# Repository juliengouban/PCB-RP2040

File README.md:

# PCB-RP2040

We've realized an electronic board based on the RP2040.
This microcontroller has 2 MB of flash memory, providing ample storage space for programs and data. It has 26 digital I/O pins, 3 of which can be used as analog inputs.
The RP20240 is used for the Raspberry Pico board and is programmable in micro-Python or directly with Arduino Ide.
We developed the board on Kicad and had it manufactured on jpclb. It costs around 17 euros per board, and is a 2-layer board measuring 2.7cm x 2 cm. You can find the files on our github.

<h1> Electronic diagram</h1>
We'll now take a closer look at how our electronic board works: 

For powering the circuit, we've used a Micro USB type B connector to supply our board with 5V. As the RP2040 uses 3.3V, we've fitted a regulator to convert 5V to +3.3V: 

This is where you'll find the 128-megabit flash memory to store the program. The 2-pin connector allows you to force USB boot:

The 12Mhz crystal provides the clock for our RP2040 microcontroller:

We have added a LED to be programmed on GPIO18 to check that our card is working properly: 

Finally, we have the RP2040 microncontroller. It is supplied with 3.3V with decoupling capacitors:

<h1>PCB Design</h1>

The board is a 2-layer design. On the top you can see the 3.3V regulator and the Micro-USB type B connector.
In the middle of the board you'll find the flash memory and the RP2040 microcontroller.
At the bottom of the board you'll find the 2-pin USB boot connector and the 12Mhz quartz crystal.
A ground plane has been created on the TOP layer to connect all the GNDs together.

Here are the 3d and top layer views of the PCB:

Here is a 3d view of the PCB:

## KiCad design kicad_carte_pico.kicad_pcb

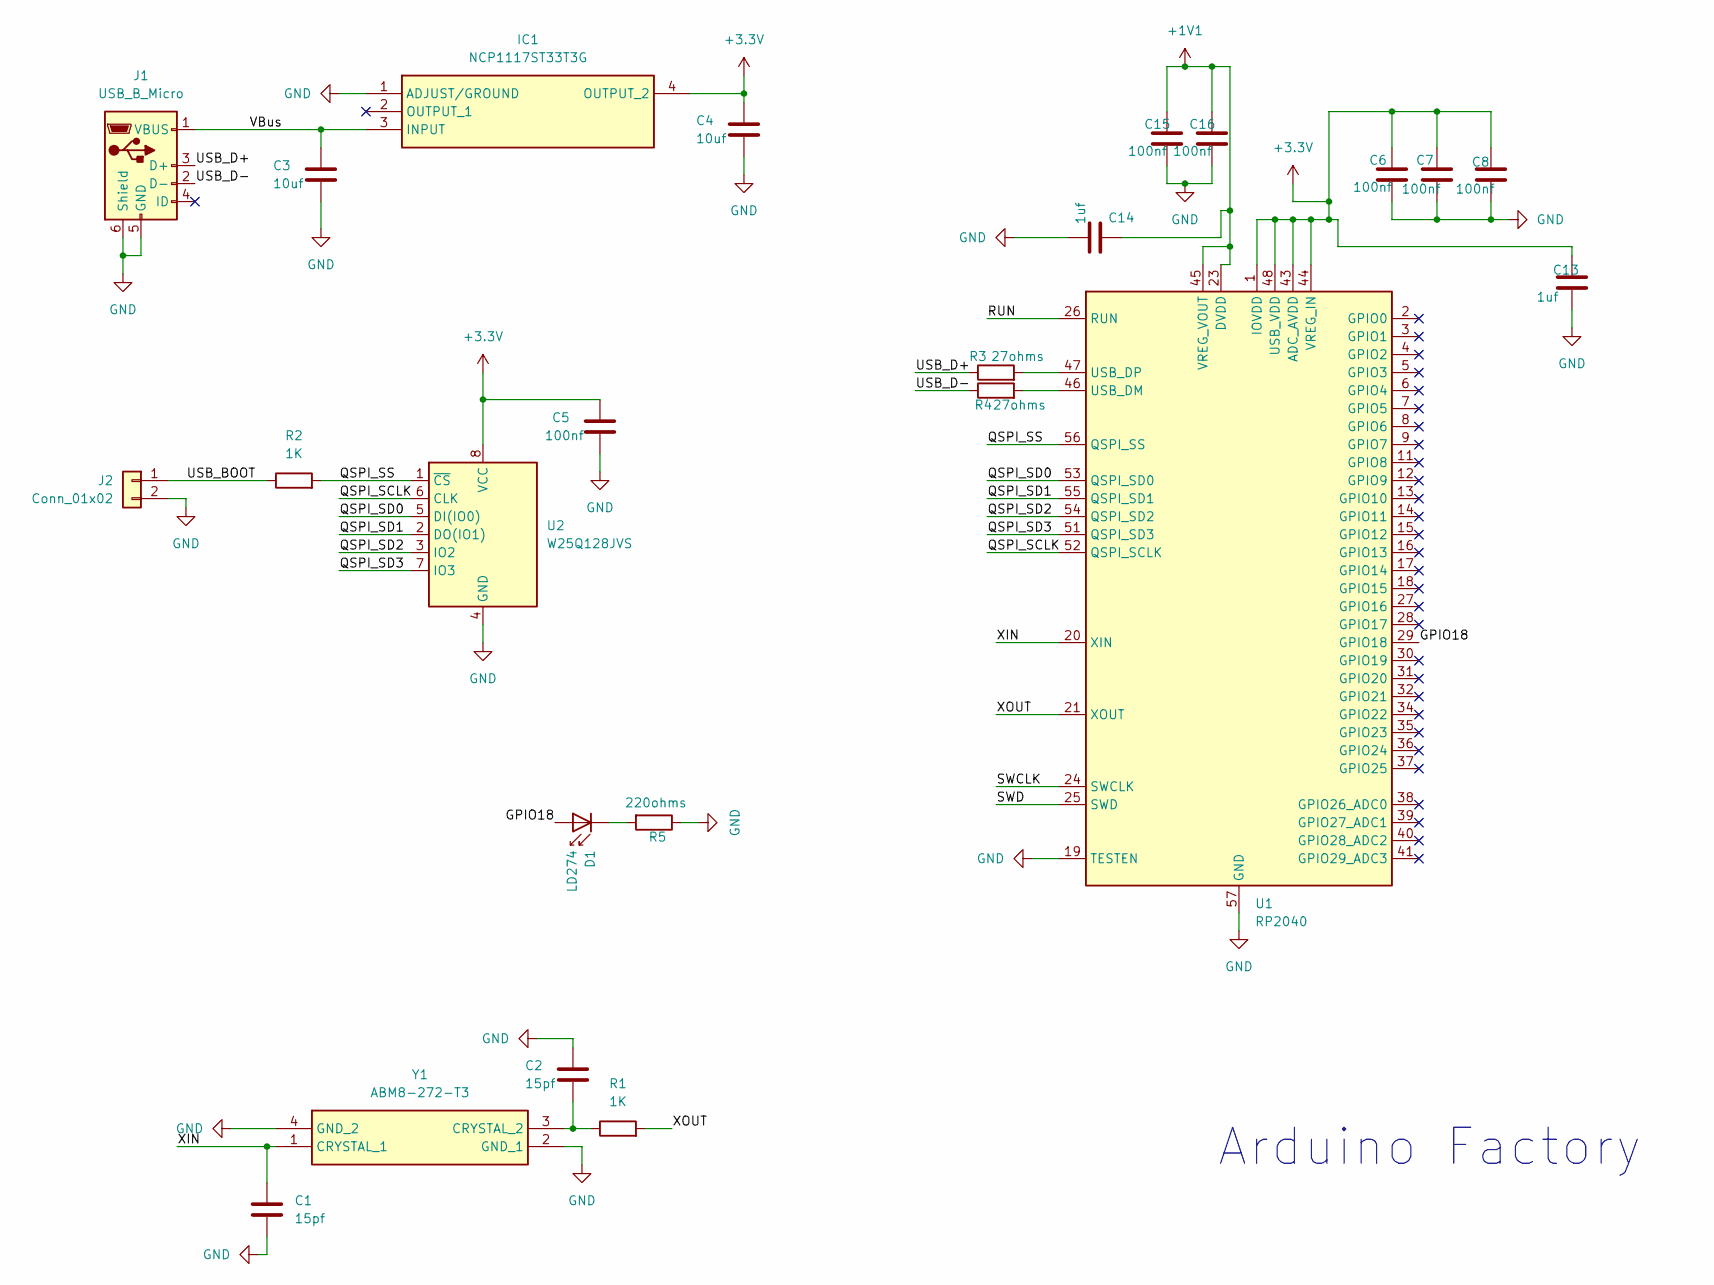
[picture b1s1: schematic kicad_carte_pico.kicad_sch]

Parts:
C1, C2: 15pf; C_0402_1005Metric
C3, C4: 10uf; C_0402_1005Metric
C5, C6, C7, C8, C15, C16: 100nf; C_0402_1005Metric
C13, C14: 1uf; C_0402_1005Metric
D1: LD274; LED_0402_1005Metric
IC1: NCP1117ST33T3G; SOT230P700X180-4N; Manufacturer_Part_Number NCP1117ST33T3G; Mouser Part Number 863-NCP1117ST33T3G
J1: USB_B_Micro; USB_Micro-B_Amphenol_10103594-0001LF_Horizontal
J2: Conn_01x02; PinHeader_1x02_P1.27mm_Vertical
R1, R2: 1K; R_0402_1005Metric
R3, R4: 27ohms; R_0402_1005Metric
R5: 220ohms; R_0402_1005Metric
U1: RP2040; QFN-56-1EP_7x7mm_P0.4mm_EP3.2x3.2mm
U2: W25Q128JVS; SOIC-8_5.23x5.23mm_P1.27mm
Y1: ABM8-272-T3; ABM8272T3; Mouser Part Number 815-ABM8-272-T3

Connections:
+1V1: C14.1, C15.1, C16.1, U1.23 (DVDD), U1.45 (VREG_VOUT), U1.50 (DVDD)
+3.3V: C4.1, C5.1, C6.1, C7.1, C8.1, C13.1, IC1.4 (OUTPUT_2), U1.1 (IOVDD), U1.10 (IOVDD), U1.22 (IOVDD), U1.33 (IOVDD), U1.42 (IOVDD), U1.43 (ADC_AVDD), U1.44 (VREG_IN), U1.48 (USB_VDD), U1.49 (IOVDD), U2.8 (VCC)
/GPIO18: D1.2 (A), U1.29 (GPIO18)
/QSPI_SCLK: U1.52 (QSPI_SCLK), U2.6 (CLK)
/QSPI_SD0: U1.53 (QSPI_SD0), U2.5 (DI(IO0))
/QSPI_SD1: U1.55 (QSPI_SD1), U2.2 (DO(IO1))
/QSPI_SD2: U1.54 (QSPI_SD2), U2.3 (IO2)
/QSPI_SD3: U1.51 (QSPI_SD3), U2.7 (IO3)
/QSPI_SS: R2.2, U1.56 (QSPI_SS), U2.1 (~CS)
/RUN: U1.26 (RUN)
/SWCLK: U1.24 (SWCLK)
/SWD: U1.25 (SWD)
/USB_BOOT: J2.1, R2.1
/USB_D+: J1.3 (D+), R3.1
/USB_D-: J1.2 (D-), R4.1
/VBus: C3.1, IC1.3 (INPUT), J1.1 (VBUS)
/XIN: C1.1, U1.20 (XIN), Y1.1 (CRYSTAL_1)
/XOUT: R1.2, U1.21 (XOUT)
GND: C1.2, C2.1, C3.2, C4.2, C5.2, C6.2, C7.2, C8.2, C13.2, C14.2, C15.2, C16.2, IC1.1 (ADJUST/GROUND), J1.5 (GND), J1.6 (Shield), J2.2, R5.1, U1.19 (TESTEN), U1.57 (GND), U2.4 (GND), Y1.2 (GND_1), Y1.4 (GND_2)
unnamed: D1.1 (K), R5.2
unnamed: R4.2, U1.46 (USB_DM)
unnamed: R3.2, U1.47 (USB_DP)
unnamed: C2.2, R1.1, Y1.3 (CRYSTAL_2)

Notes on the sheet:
Arduino Factory

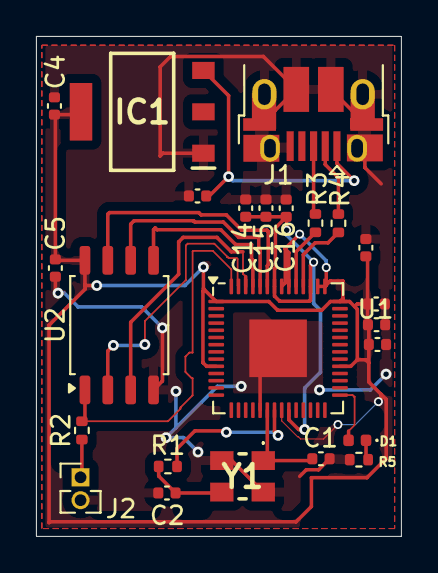
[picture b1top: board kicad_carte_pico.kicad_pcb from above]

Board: 2 copper layers, 20.3 x 27.8 mm, 24 parts (0 on the bottom side), 20 nets.

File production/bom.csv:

Designator,Footprint,Quantity,Value,LCSC Part #
"C1, C2",0402,2,15pf,
"C13, C14",0402,2,1uf,
"C15, C16, C5, C6, C7, C8",0402,6,100nf,
"C3, C4",0402,2,10uf,
D1,0402,1,LD274,
IC1,SOT230P700X180-4N,1,NCP1117ST33T3G,
J1,USB_Micro-B_Amphenol_10103594-0001LF_Horizontal,1,USB_B_Micro,
J2,PinHeader_1x02_P1.27mm_Vertical,1,Conn_01x02,
"R1, R2",0402,2,1K,
"R3, R4",0402,2,27ohms,
R5,0402,1,220ohms,
U1,QFN-56-1EP_7x7mm_P0.4mm_EP3.2x3.2mm,1,RP2040,
U2,SOIC-8_5.23x5.23mm_P1.27mm,1,W25Q128JVS,
Y1,ABM8272T3,1,ABM8-272-T3,

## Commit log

2024-11-02 Add files via upload
    Kicad Project RP2040 board
